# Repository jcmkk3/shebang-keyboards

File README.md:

# !#/keyboards/
A collection of keyboards I'm working on, generated using [Ergogen](https://github.com/mrzealot/ergogen)

### ⚠️ These keyboards have not been tested yet

The `pcb` and `gerber` folders for each keyboard contain the routed PCBs.  
`ergogen` contains the Ergogen yaml each layout was generated from.

To generate the PCBs from scratch to `ergogen/output` run;  
`npm install && npm run gen`

### - [tuck-n-roll](./tuck-n-roll)
36 key keyboard with two tucky thumb encoders

### - [plank](./plank)
A Planck-like keyboard

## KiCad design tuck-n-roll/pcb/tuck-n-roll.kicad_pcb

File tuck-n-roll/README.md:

## #!/kb/tuck-n-roll

36 key keyboard with two tucky thumb encoders

To regenerate the PCBs to `ergogen/output` run;  
`npm install && npm run gen`

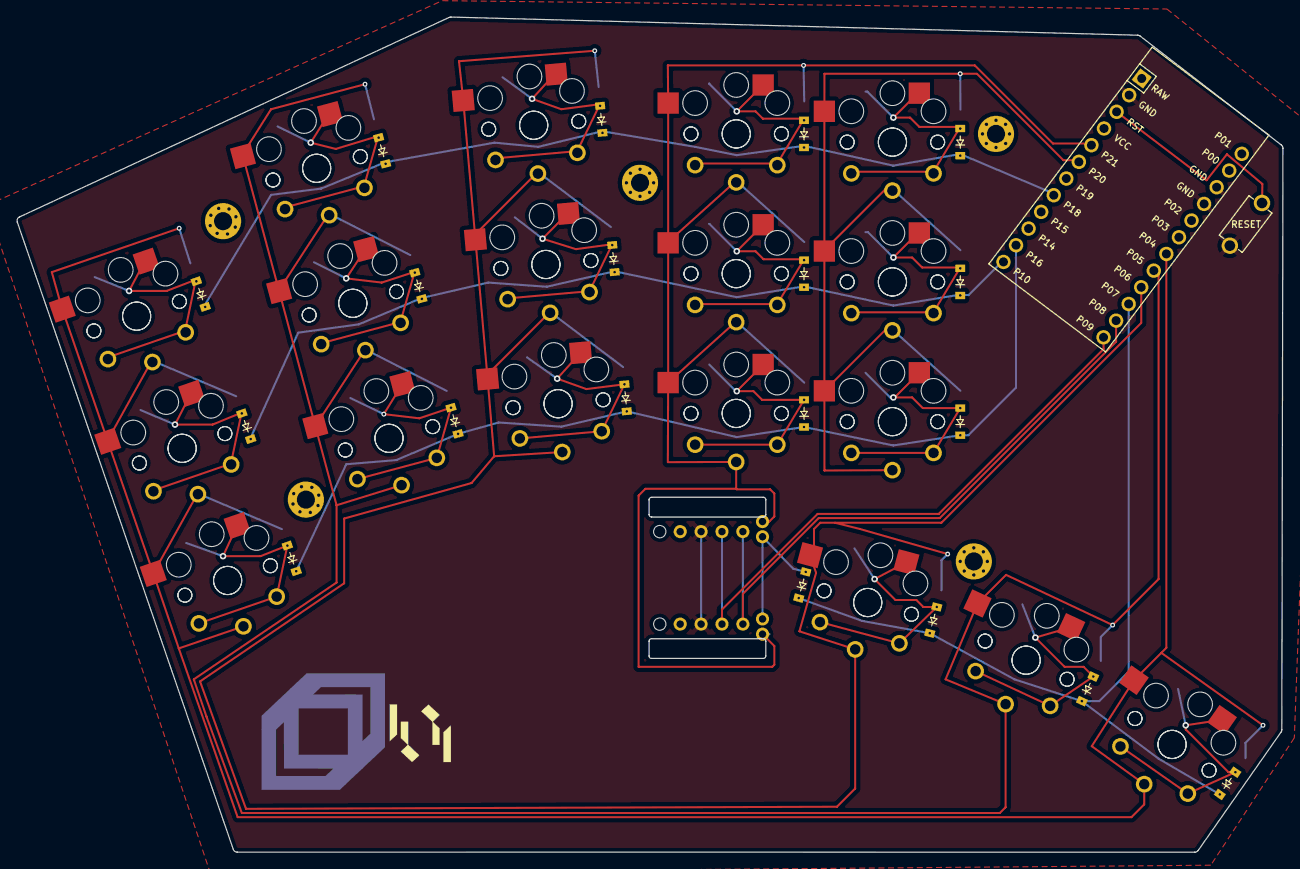
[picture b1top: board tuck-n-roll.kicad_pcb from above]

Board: 2 copper layers, 154.0 x 101.6 mm, 62 parts (0 on the bottom side), 29 nets.

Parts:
B1: SW_RST; TACT_SWITCH_TVBP06
D1, D2, D3, D4, D5, D6, D7, D8, D9, D10, D11, D12, D13, D14, D15, D16, D17, D18, D19: ComboDiode
HOLE1, HOLE2, HOLE3, HOLE4, HOLE5: MountingHole_2.2mm_M2_Pad_Via
MCU1: ProMicro
S1, S2, S3, S4, S5, S6, S7, S8, S9, S10, S11, S12, S13, S14, S15, S16, S17, S18, S19, S20, S21, S22, S23, S24, S25, S26, S27, S28, S29, S30, S31, S32, S33, S34, S35, S36: PG1350

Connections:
GND: B1.1, MCU1.2, MCU1.15, MCU1.16
P4: MCU1.19, S1.2, S2.2, S3.2, S4.2, S5.2, S6.2, S35.2, S36.2
P5: MCU1.20, S7.2, S8.2, S9.2, S10.2, S11.2, S12.2, S33.2, S34.2
P6: MCU1.21, S13.2, S14.2, S15.2, S16.2, S17.2, S18.2, S31.2, S32.2
P7: D16.1, D17.1, D18.1, D19.1, MCU1.22
P10: D2.1, D5.1, D8.1, D11.1, D14.1, MCU1.12
P16: D1.1, D4.1, D7.1, D10.1, D13.1, MCU1.11
P18: D3.1, D6.1, D9.1, D12.1, D15.1, MCU1.8
P20: MCU1.6, S25.2, S26.2, S27.2, S28.2, S29.2, S30.2
P21: MCU1.5, S19.2, S20.2, S21.2, S22.2, S23.2, S24.2
RST: B1.2, MCU1.3
far_thumb: D18.2, S35.1, S36.1
home_thumb: D17.2, S33.1, S34.1
index_bottom: D10.2, S19.1, S20.1
index_home: D11.2, S21.1, S22.1
index_top: D12.2, S23.1, S24.1
inner_bottom: D13.2, S25.1, S26.1
inner_home: D14.2, S27.1, S28.1
inner_top: D15.2, S29.1, S30.1
middle_bottom: D7.2, S13.1, S14.1
middle_home: D8.2, S15.1, S16.1
middle_top: D9.2, S17.1, S18.1
near_thumb: D16.2, S31.1, S32.1
pinky_bottom: D1.2, S1.1, S2.1
pinky_home: D2.2, S3.1, S4.1
pinky_top: D3.2, S5.1, S6.1
ring_bottom: D4.2, S7.1, S8.1
ring_home: D5.2, S9.1, S10.1
ring_top: D6.2, S11.1, S12.1

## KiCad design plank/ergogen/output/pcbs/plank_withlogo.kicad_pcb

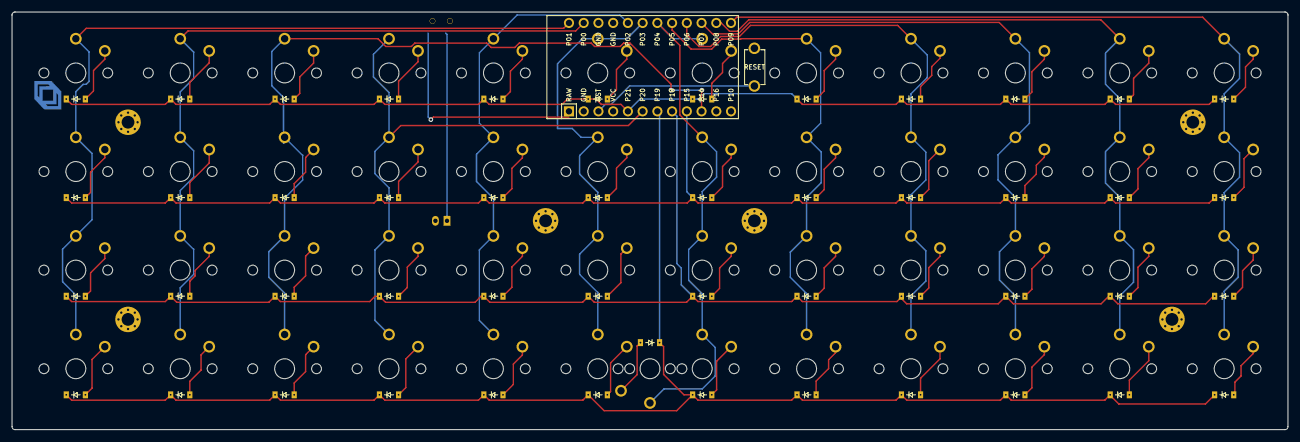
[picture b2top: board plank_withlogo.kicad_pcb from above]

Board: 2 copper layers, 220.0 x 72.0 mm, 108 parts (0 on the bottom side), 69 nets.

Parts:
B1: SW_RST; TACT_SWITCH_TVBP06
D1, D2, D3, D4, D5, D6, D7, D8, D9, D10, D11, D12, D13, D14, D15, D16, D17, D18, D19, D20, D21, D22, D23, D24, D25, D26, D27, D28, D29, D30, D31, D32, D33, D34, D35, D36, D37, D38, D39, D40, D41, D42, D43, D44, D45, D46, D47, D48, D49: ComboDiode
HOLE1, HOLE2, HOLE3, HOLE4, HOLE5, HOLE6: MountingHole_2.2mm_M2_Pad_Via
JST1: JST_PH_S2B-PH-K_02x2.00mm_Angled
MCU1: ProMicro
S1, S2, S3, S4, S5, S6, S7, S8, S9, S10, S11, S12, S13, S14, S15, S16, S17, S18, S19, S20, S21, S22, S23, S24, S25, S26, S27, S28, S29, S30, S31, S32, S33, S34, S35, S36, S37, S38, S39, S40, S41, S42, S43, S44, S45, S46, S47, S48, S49: PG1350
T1: SPDT_C128955

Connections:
BAT: JST1.1, T1.2
GND: B1.1, JST1.2, MCU1.2, MCU1.15, MCU1.16
P0: MCU1.14, S5.2, S6.2, S7.2, S8.2
P1: MCU1.13, S1.2, S2.2, S3.2, S4.2
P2: MCU1.17, S17.2, S18.2, S19.2, S20.2
P3: MCU1.18, S21.2, S22.2, S23.2, S24.2
P4: MCU1.19, S25.2, S26.2, S27.2, S28.2, S29.2
P5: MCU1.20, S30.2, S31.2, S32.2, S33.2
P6: MCU1.21, S34.2, S35.2, S36.2, S37.2
P7: MCU1.22, S38.2, S39.2, S40.2, S41.2
P8: MCU1.23, S42.2, S43.2, S44.2, S45.2
P9: MCU1.24, S46.2, S47.2, S48.2, S49.2
P14: MCU1.10, S9.2, S10.2, S11.2, S12.2
P15: D3.1, D7.1, D11.1, D15.1, D19.1, D23.1, D28.1, D32.1, D36.1, D40.1, D44.1, D48.1, MCU1.9
P18: D2.1, D6.1, D10.1, D14.1, D18.1, D22.1, D27.1, D31.1, D35.1, D39.1, D43.1, D47.1, MCU1.8
P19: D1.1, D5.1, D9.1, D13.1, D17.1, D21.1, D25.1, D26.1, D30.1, D34.1, D38.1, D42.1, D46.1, MCU1.7
P20: MCU1.6, S13.2, S14.2, S15.2, S16.2
P21: D4.1, D8.1, D12.1, D16.1, D20.1, D24.1, D29.1, D33.1, D37.1, D41.1, D45.1, D49.1, MCU1.5
RAW: MCU1.1, T1.1
RST: B1.2, MCU1.3
eight_bottom: D31.2, S31.1
eight_home: D32.2, S32.1
eight_modrow: D30.2, S30.1
eight_top: D33.2, S33.1
eleven_bottom: D43.2, S43.1
eleven_home: D44.2, S44.1
eleven_modrow: D42.2, S42.1
eleven_top: D45.2, S45.1
five_bottom: D18.2, S18.1
five_home: D19.2, S19.1
five_modrow: D17.2, S17.1
five_top: D20.2, S20.1
four_bottom: D14.2, S14.1
four_home: D15.2, S15.1
four_modrow: D13.2, S13.1
four_top: D16.2, S16.1
nine_bottom: D35.2, S35.1
nine_home: D36.2, S36.1
nine_modrow: D34.2, S34.1
nine_top: D37.2, S37.1
one_bottom: D2.2, S2.1
one_home: D3.2, S3.1
one_modrow: D1.2, S1.1
one_top: D4.2, S4.1
seven_2uspacebar: D25.2, S25.1
seven_bottom: D27.2, S27.1
seven_home: D28.2, S28.1
seven_modrow: D26.2, S26.1
seven_top: D29.2, S29.1
six_bottom: D22.2, S22.1
six_home: D23.2, S23.1
six_modrow: D21.2, S21.1
six_top: D24.2, S24.1
ten_bottom: D39.2, S39.1
ten_home: D40.2, S40.1
ten_modrow: D38.2, S38.1
ten_top: D41.2, S41.1
three_bottom: D10.2, S10.1
three_home: D11.2, S11.1
three_modrow: D9.2, S9.1
three_top: D12.2, S12.1
twelve_bottom: D47.2, S47.1
twelve_home: D48.2, S48.1
twelve_modrow: D46.2, S46.1
twelve_top: D49.2, S49.1
two_bottom: D6.2, S6.1
two_home: D7.2, S7.1
two_modrow: D5.2, S5.1
two_top: D8.2, S8.1

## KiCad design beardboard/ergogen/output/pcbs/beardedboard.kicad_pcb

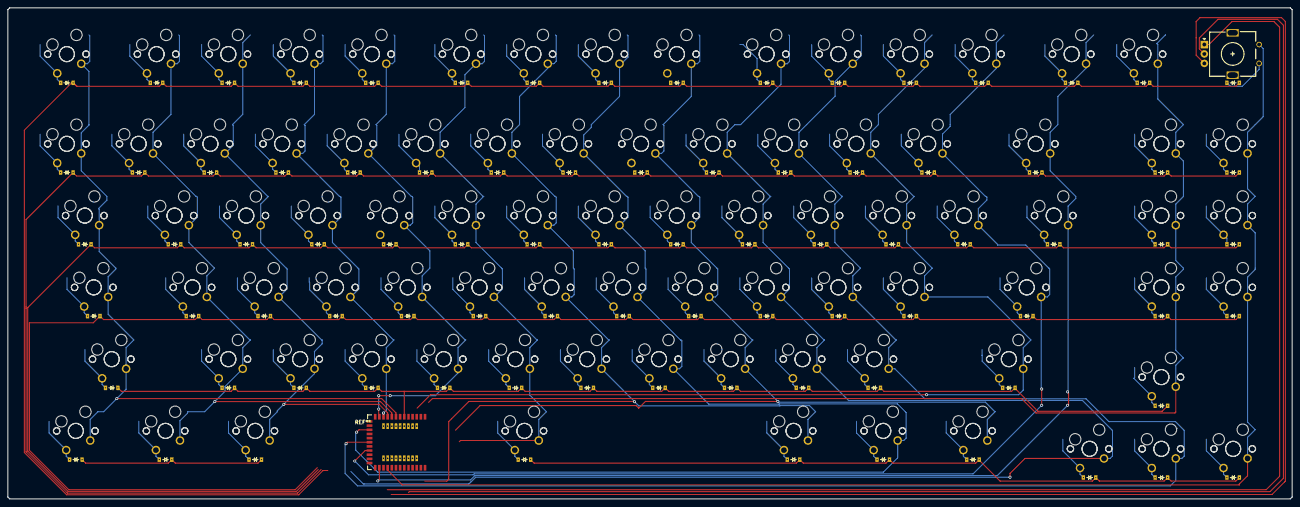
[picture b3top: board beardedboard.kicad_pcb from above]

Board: 2 copper layers, 340.0 x 130.0 mm, 257 parts (0 on the bottom side), 108 nets.

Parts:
D1, D2, D3, D4, D5, D6, D7, D8, D9, D10, D11, D12, D13, D14, D15, D16, D17, D18, D19, D20, D21, D22, D23, D24, D25, D26, D27, D28, D29, D30, D31, D32, D33, D34, D35, D36, D37, D38, D39, D40, D41, D42, D43, D44, D45, D46, D47, D48, D49, D50, D51, D52, D53, D54, D55, D56, D57, D58, D59, D60, D61, D62, D63, D64, D65, D66, D67, D68, D69, D70, D71, D72, D73, D74, D75, D76, D77, D78, D79, D80, D81, D82, D83, D84, D85, D86: ComboDiode
ROT1: rotary_encoder
S1, S2, S3, S4, S5, S6, S7, S8, S9, S10, S11, S12, S13, S14, S15, S16, S17, S18, S19, S20, S21, S22, S23, S24, S25, S26, S27, S28, S29, S30, S31, S32, S33, S34, S35, S36, S37, S38, S39, S40, S41, S42, S43, S44, S45, S46, S47, S48, S49, S50, S51, S52, S53, S54, S55, S56, S57, S58, S59, S60, S61, S62, S63, S64, S65, S66, S67, S68, S69, S70, S71, S72, S73, S74, S75, S76, S77, S78, S79, S80, S81, S82, S83, S84, S85, S86, S87, S88, S89, S90, S91, S92, S93, S94, S95, S96, S97, S98, S99, S100, S101, S102, S103, S104, S105, S106, S107, S108, S109, S110, S111, S112, S113, S114, S115, S116, S117, S118, S119, S120, S121, S122, S123, S124, S125, S126, S127, S128, S129, S130, S131, S132, S133, S134, S135, S136, S137, S138, S139, S140, S141, S142, S143, S144, S145, S146, S147, S148, S149, S150, S151, S152, S153, S154, S155, S156, S157, S158, S159, S160, S161, S162, S163, S164, S165, S166, S167, S168, S169, S170: MX

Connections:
P002: D76.1, D77.1, D78.1, D79.1, D80.1, D81.1, D82.1, D83.1, D84.1, D85.1
P003: D63.1, D64.1, D65.1, D66.1, D67.1, D68.1, D69.1, D70.1, D71.1, D72.1, D73.1, D74.1, D75.1
P004: S9.2, S10.2, S39.2, S40.2, S71.2, S72.2, S103.2, S104.2, S133.2, S134.2
P005: S11.2, S12.2, S41.2, S42.2, S73.2, S74.2, S105.2, S106.2, S135.2, S136.2, S157.2, S158.2
P007: S13.2, S14.2, S43.2, S44.2, S75.2, S76.2, S107.2, S108.2, S137.2, S138.2, S159.2, S160.2
P012: S17.2, S18.2, S47.2, S48.2, S79.2, S80.2, S111.2, S112.2, S141.2, S142.2, S163.2, S164.2
P018: S25.2, S26.2, S55.2, S56.2, S87.2, S88.2, S119.2, S120.2
P019: S23.2, S24.2, S53.2, S54.2, S85.2, S86.2, S117.2, S118.2, S147.2, S148.2
P021: S21.2, S22.2, S51.2, S52.2, S83.2, S84.2, S115.2, S116.2, S145.2, S146.2, S167.2, S168.2
P022: S27.2, S28.2, S57.2, S58.2, S89.2, S90.2
P023: S19.2, S20.2, S49.2, S50.2, S81.2, S82.2, S113.2, S114.2, S143.2, S144.2, S165.2, S166.2
P028: S1.2, S2.2, S31.2, S32.2, S63.2, S64.2, S95.2, S96.2, S125.2, S126.2, S151.2, S152.2
P029: S3.2, S4.2, S33.2, S34.2, S65.2, S66.2, S97.2, S98.2, S127.2, S128.2, S153.2, S154.2
P030: S5.2, S6.2, S35.2, S36.2, S67.2, S68.2, S99.2, S100.2, S129.2, S130.2, S155.2, S156.2
P031: S7.2, S8.2, S37.2, S38.2, S69.2, S70.2, S101.2, S102.2, S131.2, S132.2
P100: S29.2, S30.2, S59.2, S60.2, S91.2, S92.2, S121.2, S122.2, S149.2, S150.2
P103: ROT1.1, S61.2, S62.2, S93.2, S94.2, S123.2, S124.2, S169.2, S170.2
P109: S15.2, S16.2, S45.2, S46.2, S77.2, S78.2, S109.2, S110.2, S139.2, S140.2, S161.2, S162.2
P110: D1.1, D2.1, D3.1, D4.1, D5.1, D6.1, D7.1, D8.1, D9.1, D10.1, D11.1, D12.1, D13.1, D14.1, D15.1, D86.1
P111: D16.1, D17.1, D18.1, D19.1, D20.1, D21.1, D22.1, D23.1, D24.1, D25.1, D26.1, D27.1, D28.1, D29.1, D30.1, D31.1
P113: D32.1, D33.1, D34.1, D35.1, D36.1, D37.1, D38.1, D39.1, D40.1, D41.1, D42.1, D43.1, D44.1, D45.1, D46.1, D47.1
P115: D48.1, D49.1, D50.1, D51.1, D52.1, D53.1, D54.1, D55.1, D56.1, D57.1, D58.1, D59.1, D60.1, D61.1, D62.1
key1col_key1row: D1.2, S1.1, S2.1
key2col_key2row: D2.2, S3.1, S4.1
key3col_key3row: D3.2, S5.1, S6.1
key4col_key4row: D4.2, S7.1, S8.1
key5col_key5row: D5.2, S9.1, S10.1
key6col_key6row: D6.2, S11.1, S12.1
key7col_key7row: D7.2, S13.1, S14.1
key8col_key8row: D8.2, S15.1, S16.1
key9col_key9row: D9.2, S17.1, S18.1
key10col_key10row: D10.2, S19.1, S20.1
key11col_key11row: D11.2, S21.1, S22.1
key12col_key12row: D12.2, S23.1, S24.1
key13col_key13row: D13.2, S25.1, S26.1
key14col_key14row: D14.2, S27.1, S28.1
key15col_key15row: D15.2, S29.1, S30.1
key16diode: D86.2, ROT1.2
key17col_key17row: D16.2, S31.1, S32.1
key18col_key18row: D17.2, S33.1, S34.1
key19col_key19row: D18.2, S35.1, S36.1
key20col_key20row: D19.2, S37.1, S38.1
key21col_key21row: D20.2, S39.1, S40.1
key22col_key22row: D21.2, S41.1, S42.1
key23col_key23row: D22.2, S43.1, S44.1
key24col_key24row: D23.2, S45.1, S46.1
key25col_key25row: D24.2, S47.1, S48.1
key26col_key26row: D25.2, S49.1, S50.1
key27col_key27row: D26.2, S51.1, S52.1
key28col_key28row: D27.2, S53.1, S54.1
key29col_key29row: D28.2, S55.1, S56.1
key30col_key30row: D29.2, S57.1, S58.1
key31col_key31row: D30.2, S59.1, S60.1
key32col_key32row: D31.2, S61.1, S62.1
key33col_key33row: D32.2, S63.1, S64.1
key34col_key34row: D33.2, S65.1, S66.1
key35col_key35row: D34.2, S67.1, S68.1
key36col_key36row: D35.2, S69.1, S70.1
key37col_key37row: D36.2, S71.1, S72.1
key38col_key38row: D37.2, S73.1, S74.1
key39col_key39row: D38.2, S75.1, S76.1
key40col_key40row: D39.2, S77.1, S78.1
key41col_key41row: D40.2, S79.1, S80.1
key42col_key42row: D41.2, S81.1, S82.1
key43col_key43row: D42.2, S83.1, S84.1
key44col_key44row: D43.2, S85.1, S86.1
key45col_key45row: D44.2, S87.1, S88.1
key46col_key46row: D45.2, S89.1, S90.1
key47col_key47row: D46.2, S91.1, S92.1
key48col_key48row: D47.2, S93.1, S94.1
key49col_key49row: D48.2, S95.1, S96.1
key50col_key50row: D49.2, S97.1, S98.1
key51col_key51row: D50.2, S99.1, S100.1
key52col_key52row: D51.2, S101.1, S102.1
key53col_key53row: D52.2, S103.1, S104.1
key54col_key54row: D53.2, S105.1, S106.1
key55col_key55row: D54.2, S107.1, S108.1
key56col_key56row: D55.2, S109.1, S110.1
key57col_key57row: D56.2, S111.1, S112.1
key58col_key58row: D57.2, S113.1, S114.1
key59col_key59row: D58.2, S115.1, S116.1
key60col_key60row: D59.2, S117.1, S118.1
key61col_key61row: D60.2, S119.1, S120.1
key62col_key62row: D61.2, S121.1, S122.1
key63col_key63row: D62.2, S123.1, S124.1
key64col_key64row: D63.2, S125.1, S126.1
key65col_key65row: D64.2, S127.1, S128.1
key66col_key66row: D65.2, S129.1, S130.1
key67col_key67row: D66.2, S131.1, S132.1
key68col_key68row: D67.2, S133.1, S134.1
key69col_key69row: D68.2, S135.1, S136.1
key70col_key70row: D69.2, S137.1, S138.1
key71col_key71row: D70.2, S139.1, S140.1
key72col_key72row: D71.2, S141.1, S142.1
key73col_key73row: D72.2, S143.1, S144.1
key74col_key74row: D73.2, S145.1, S146.1
key75col_key75row: D74.2, S147.1, S148.1
key76col_key76row: D75.2, S149.1, S150.1
key77col_key77row: D76.2, S151.1, S152.1
key78col_key78row: D77.2, S153.1, S154.1
key79col_key79row: D78.2, S155.1, S156.1
key80col_key80row: D79.2, S157.1, S158.1
key81col_key81row: D80.2, S159.1, S160.1
key82col_key82row: D81.2, S161.1, S162.1
key83col_key83row: D82.2, S163.1, S164.1
key84col_key84row: D83.2, S165.1, S166.1
key85col_key85row: D84.2, S167.1, S168.1
key86col_key86row: D85.2, S169.1, S170.1

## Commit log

2021-08-15 Initial readme
2021-08-15 (WIP) add tuck-n-roll
2021-08-16 WIP attempt at a thing
2021-08-17 Column routing
2021-08-18 fix choc nets
2021-08-18 Add package.json
2021-08-18 Add !#/kb/tuck-n-roll to readme
2021-08-26 Fix nets
2021-08-27 Add 'tuck-n-roll'
2021-08-27 Use KLE-Serial with prepare script
2021-08-27 Add image for tuck-n-roll
2021-08-27 Add tuck-n-roll keyboard (#1)
2021-08-27 Add Ergogen link to README
2021-08-27 change diode via_in_pad param
2021-08-27 Use patched ergogen branch
2021-08-27 Add tuck-n-roll image
2021-09-03 add beardboard config
2021-09-03 add kleconfig.json for beardboard
2021-09-03 Add svgtest.yml
2021-09-05 Use mveerd branch
2021-09-05 Plank (#3)
2021-09-07 Add Plank mounting holes
2021-09-07 Add logo to Plank
2021-09-08 pinout, routes, encoder
2021-09-08 Finish matrix/mcu routes
2021-09-08 Add program/debug traces
2021-09-08 update config
2021-09-08 Tuck n roll config update (#4)
2021-09-09 .gitignore all output directories
2021-09-09 Add warning to say keyboards have not been tested yet
2021-09-13 test
2021-09-13 Update tuck-n-roll to latest version
2021-10-15 (fix) Tuck-n-roll choc keycap outline size
